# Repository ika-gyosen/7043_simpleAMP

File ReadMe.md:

View this project on [CADLAB.io](https://cadlab.io/project/1020). 

# ReadMe

## NJU7043 

[7043 DataSheet](https://www.njr.co.jp/products/semicon/PDF/NJU7043_J.pdf)

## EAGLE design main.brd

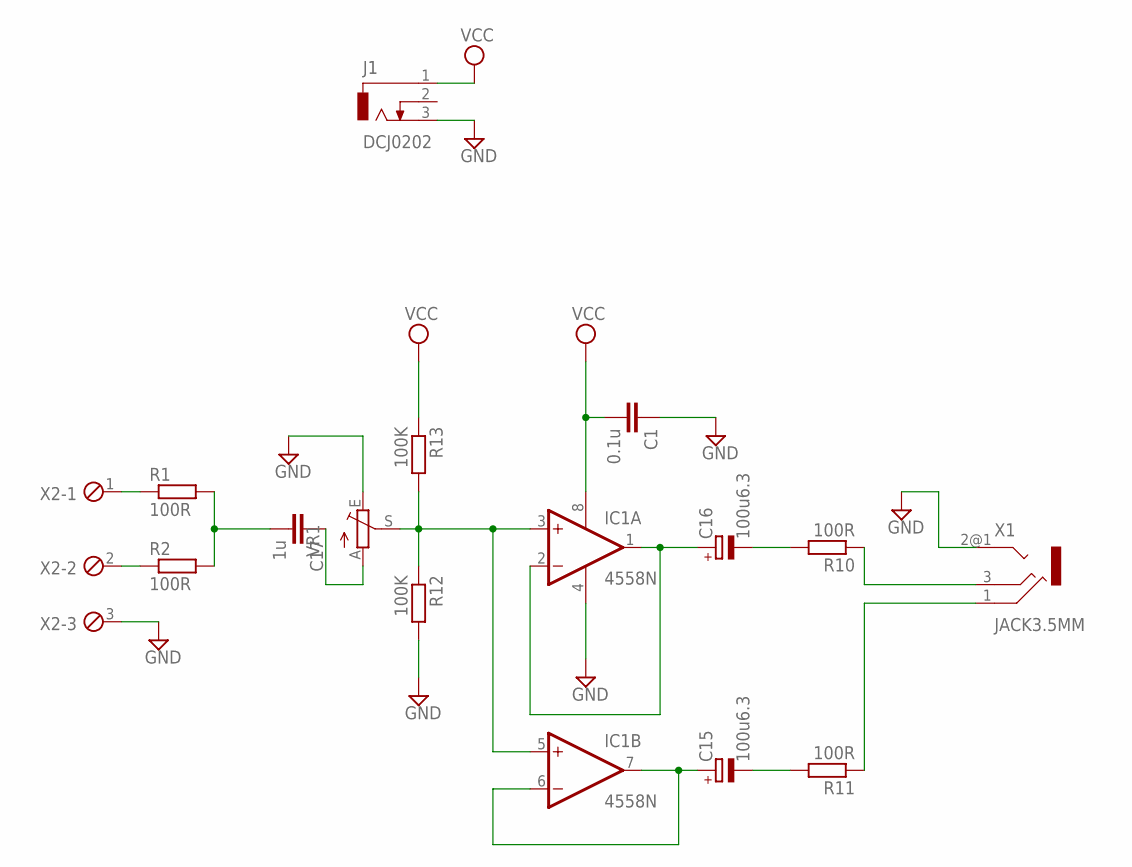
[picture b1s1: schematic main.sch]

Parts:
C1: 0.1u; C050-024X044
C15, C16: 100u6.3; TAP5-45
C17: 1u; C050-024X044
IC1: 4558N; DIP08
J1: DCJ0202
R1, R2, R10, R11: 100R; 0207(1/4W)
R12, R13: 100K; 0207(1/4W)
VR1: KIT-TRIMPOTPOT_ST; POT-ST
X1: JACK3.5MM; MJ-8435
X2: MPT3; 3POL254

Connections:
GND: C1.1, IC1.4 (V-), J1.3, R12.2, VR1.E, X1.2@1 (2), X2.3
unnamed: R10.1, X1.3
unnamed: R11.1, X1.1
unnamed: R2.1, X2.2
unnamed: R1.1, X2.1
unnamed: C17.2, R1.2, R2.2
unnamed: C17.1, VR1.A
unnamed: IC1.3 (+IN), IC1.5 (+IN), R12.1, R13.2, VR1.S
unnamed: C16.+, IC1.1 (OUT), IC1.2 (-IN)
unnamed: C16.-, R10.2
unnamed: C15.+, IC1.6 (-IN), IC1.7 (OUT)
unnamed: C15.-, R11.2
VCC: C1.2, IC1.8 (V+), J1.1, R13.1

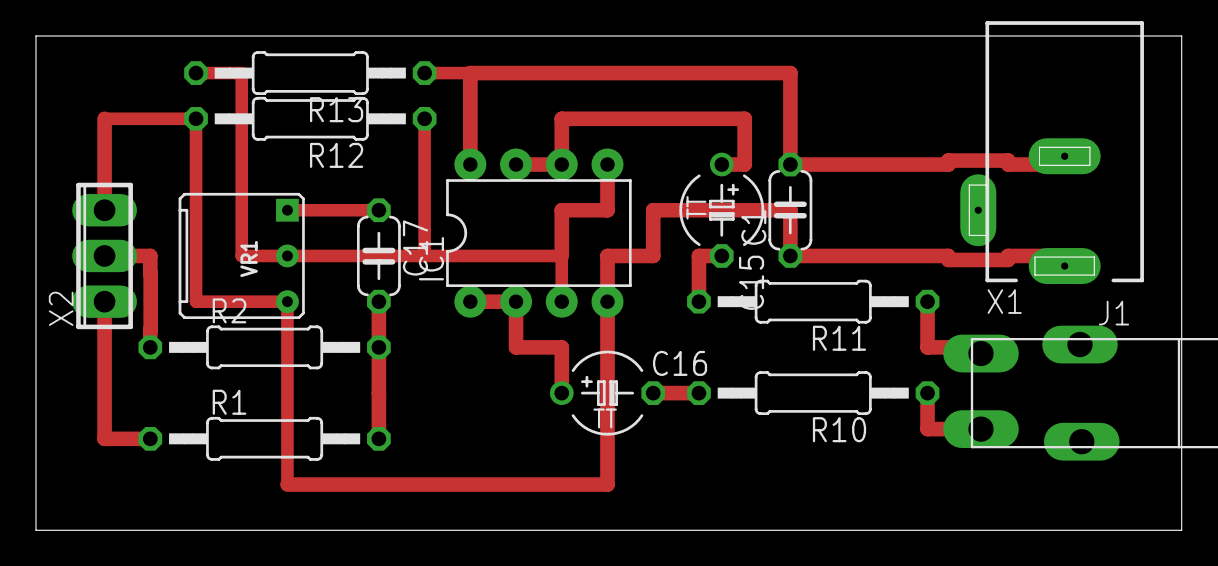
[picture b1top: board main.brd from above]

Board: 2 copper layers, 63.7 x 27.5 mm, 15 parts (0 on the bottom side), 13 nets.

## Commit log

2018-05-12 first
2018-05-12 Backlink to CADLAB.io has been added.
2018-05-19 Fix of annotation comment
